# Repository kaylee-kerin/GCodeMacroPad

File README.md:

This is a keypad I built for my CNC setup.  It sends GCode to the controller directly, allowing for PC-less local control of a stand-alone CNC controller.

* It's mostly custom coded for my needs, each button having a defined program for sending its gcode.
* It has some functionality for button groups (such as selected the X, Y, Z, or A Axis in a modal fashion), as well as jog increments.
* It has functionality for command queueing
* Multiple presses of the jog button are smooth and can be cycle-counted. ie: 5 presses of 0.001", goes 0.005"
* Checks status for alarm, and alerts.

The Keycaps I used were simple ones that allow you to place a paper label under a plastic lid.  When programming, the button order is as shown on my svg label template.

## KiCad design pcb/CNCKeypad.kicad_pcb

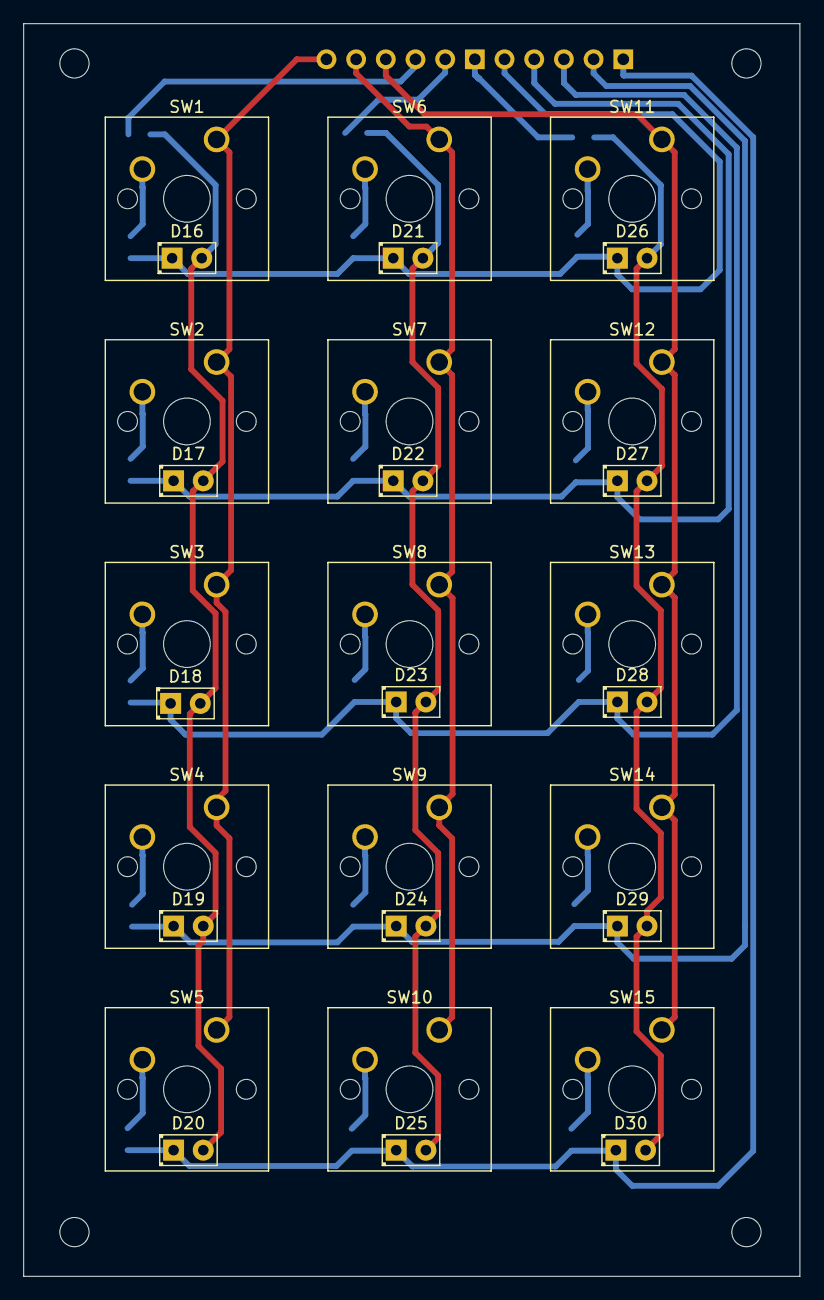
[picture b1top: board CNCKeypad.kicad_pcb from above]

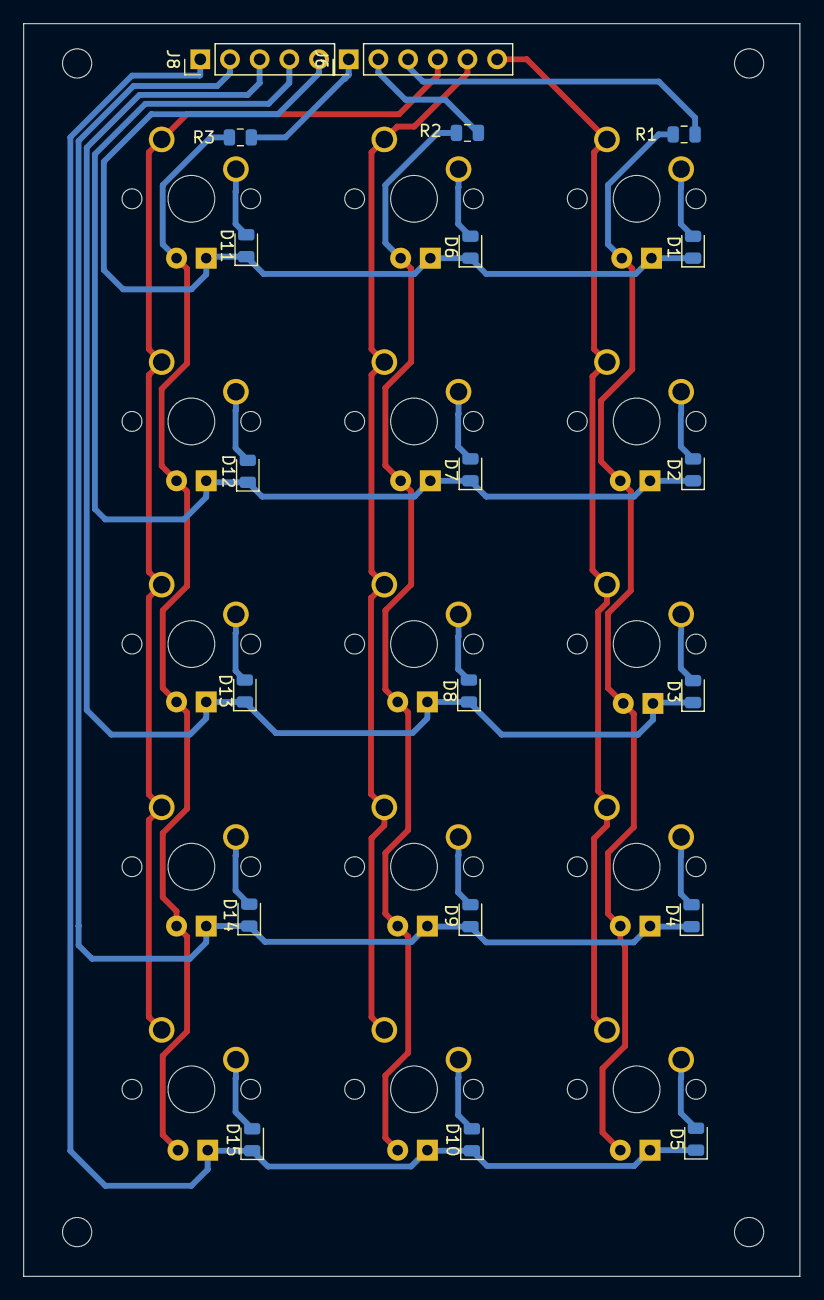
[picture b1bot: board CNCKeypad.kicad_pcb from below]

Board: 2 copper layers, 66.4 x 107.2 mm, 50 parts (20 on the bottom side), 29 nets.

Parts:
D1, D2, D3, D4, D5, D6, D7, D8, D9, D10, D11, D12, D13, D14, D15: D_Small; D_0805_2012Metric
D16, D17, D18, D19, D20, D21, D22, D23, D24, D25, D26, D27, D28, D29, D30: LED; LED_D2.0mm_W4.8mm_H2.5mm_FlatTop
J6: Conn_01x06_Male; PinHeader_1x06_P2.54mm_Vertical
J8: Conn_01x05_Male; PinHeader_1x05_P2.54mm_Vertical
R1, R2, R3: 330; R_0805_2012Metric
SW1, SW2, SW3, SW4, SW5, SW6, SW7, SW8, SW9, SW10, SW11, SW12, SW13, SW14, SW15: SW_Push_45deg; SW_Cherry_MX1A_1.00u_PCB

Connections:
unnamed: D1.1, D6.1, D11.1, D16.1, D21.1, D26.1, J8.5
unnamed: D1.2, SW1.2
unnamed: D2.2, SW2.2
unnamed: D3.2, SW3.2
unnamed: D4.2, SW4.2
unnamed: D5.2, SW5.2
unnamed: D6.2, SW6.2
unnamed: D7.2, SW7.2
unnamed: D8.2, SW8.2
unnamed: D9.2, SW9.2
unnamed: D5.1, D10.1, D15.1, D20.1, D25.1, D30.1, J8.1
unnamed: D10.2, SW10.2
unnamed: D11.2, SW11.2
unnamed: D2.1, D7.1, D12.1, D17.1, D22.1, D27.1, J8.4
unnamed: D12.2, SW12.2
unnamed: D3.1, D8.1, D13.1, D18.1, D23.1, D28.1, J8.3
unnamed: D13.2, SW13.2
unnamed: D4.1, D9.1, D14.1, D19.1, D24.1, D29.1, J8.2
unnamed: D14.2, SW14.2
unnamed: D15.2, SW15.2
unnamed: D16.2, D17.2, D18.2, D19.2, D20.2, R1.2
unnamed: D21.2, D22.2, D23.2, D24.2, D25.2, R2.2
unnamed: D26.2, D27.2, D28.2, D29.2, D30.2, R3.2
unnamed: J6.1, R3.1
unnamed: J6.2, R2.1
unnamed: J6.3, R1.1
unnamed: J6.4, SW11.1, SW12.1, SW13.1, SW14.1, SW15.1
unnamed: J6.5, SW6.1, SW7.1, SW8.1, SW9.1, SW10.1
unnamed: J6.6, SW1.1, SW2.1, SW3.1, SW4.1, SW5.1

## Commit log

2025-11-14 Initial prototype code for the CNC GCode Control Panel.
2025-11-14 Cleanup the schematic page, it was all squished.
2025-11-14 Add some explanation of the row/column scan pin config.
2025-11-14 Some pictures for the readme
2025-11-14 Initial project readme
2025-11-14 Add the current gerbers for the keypad.
